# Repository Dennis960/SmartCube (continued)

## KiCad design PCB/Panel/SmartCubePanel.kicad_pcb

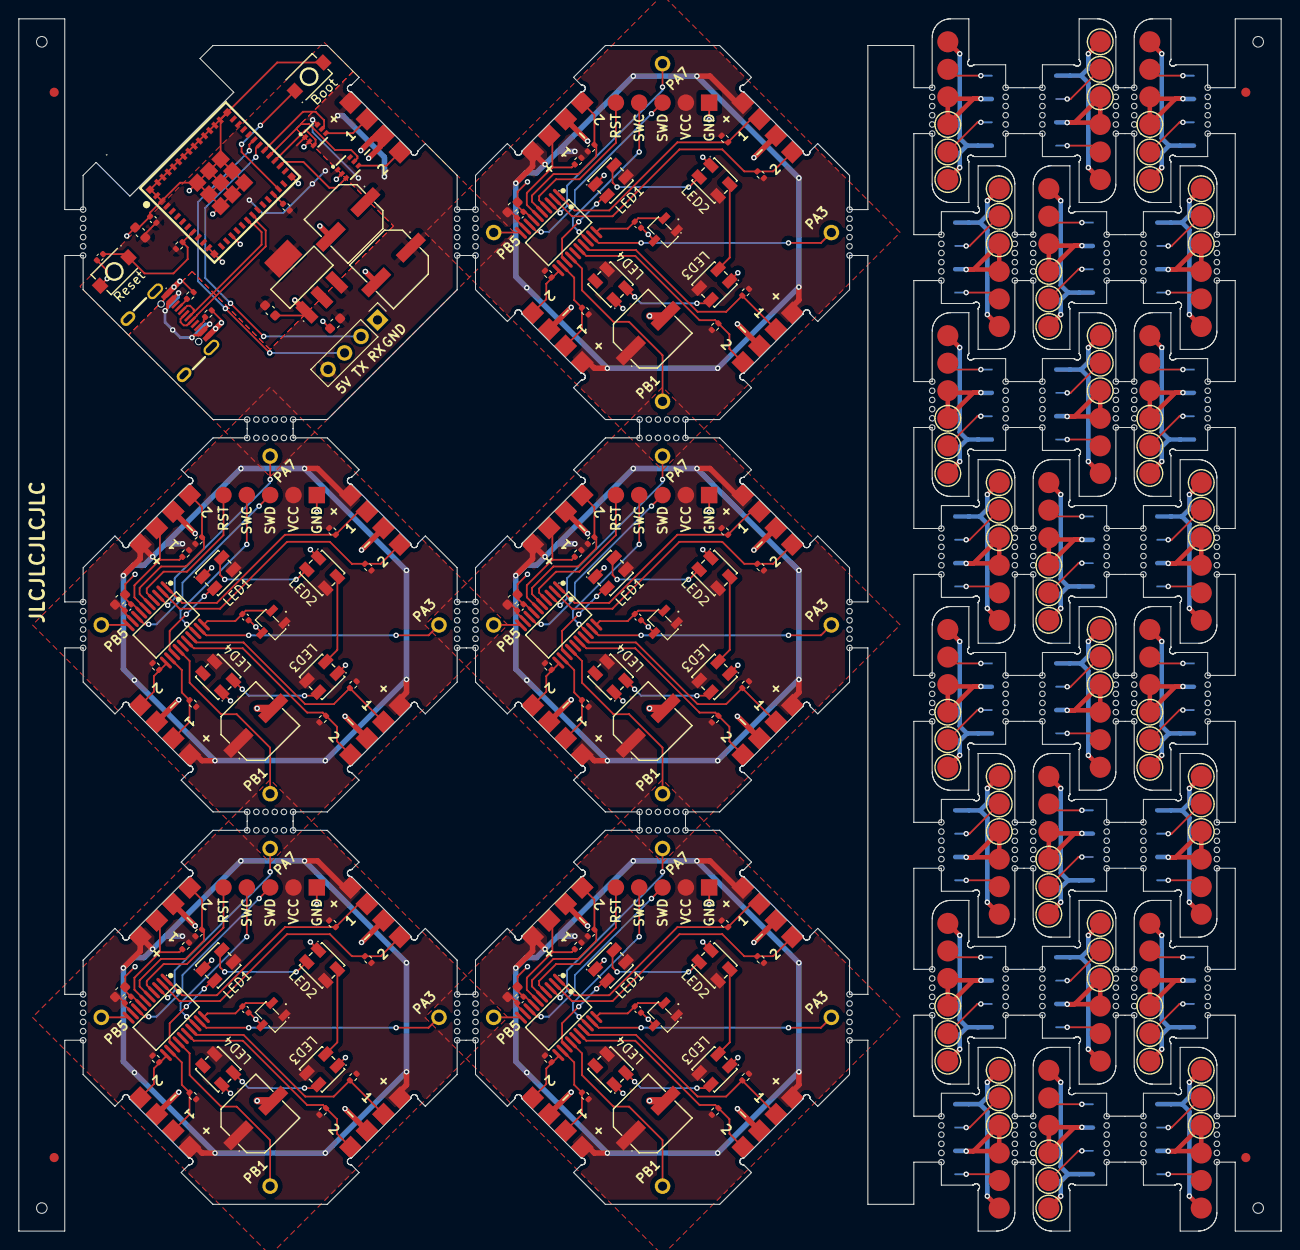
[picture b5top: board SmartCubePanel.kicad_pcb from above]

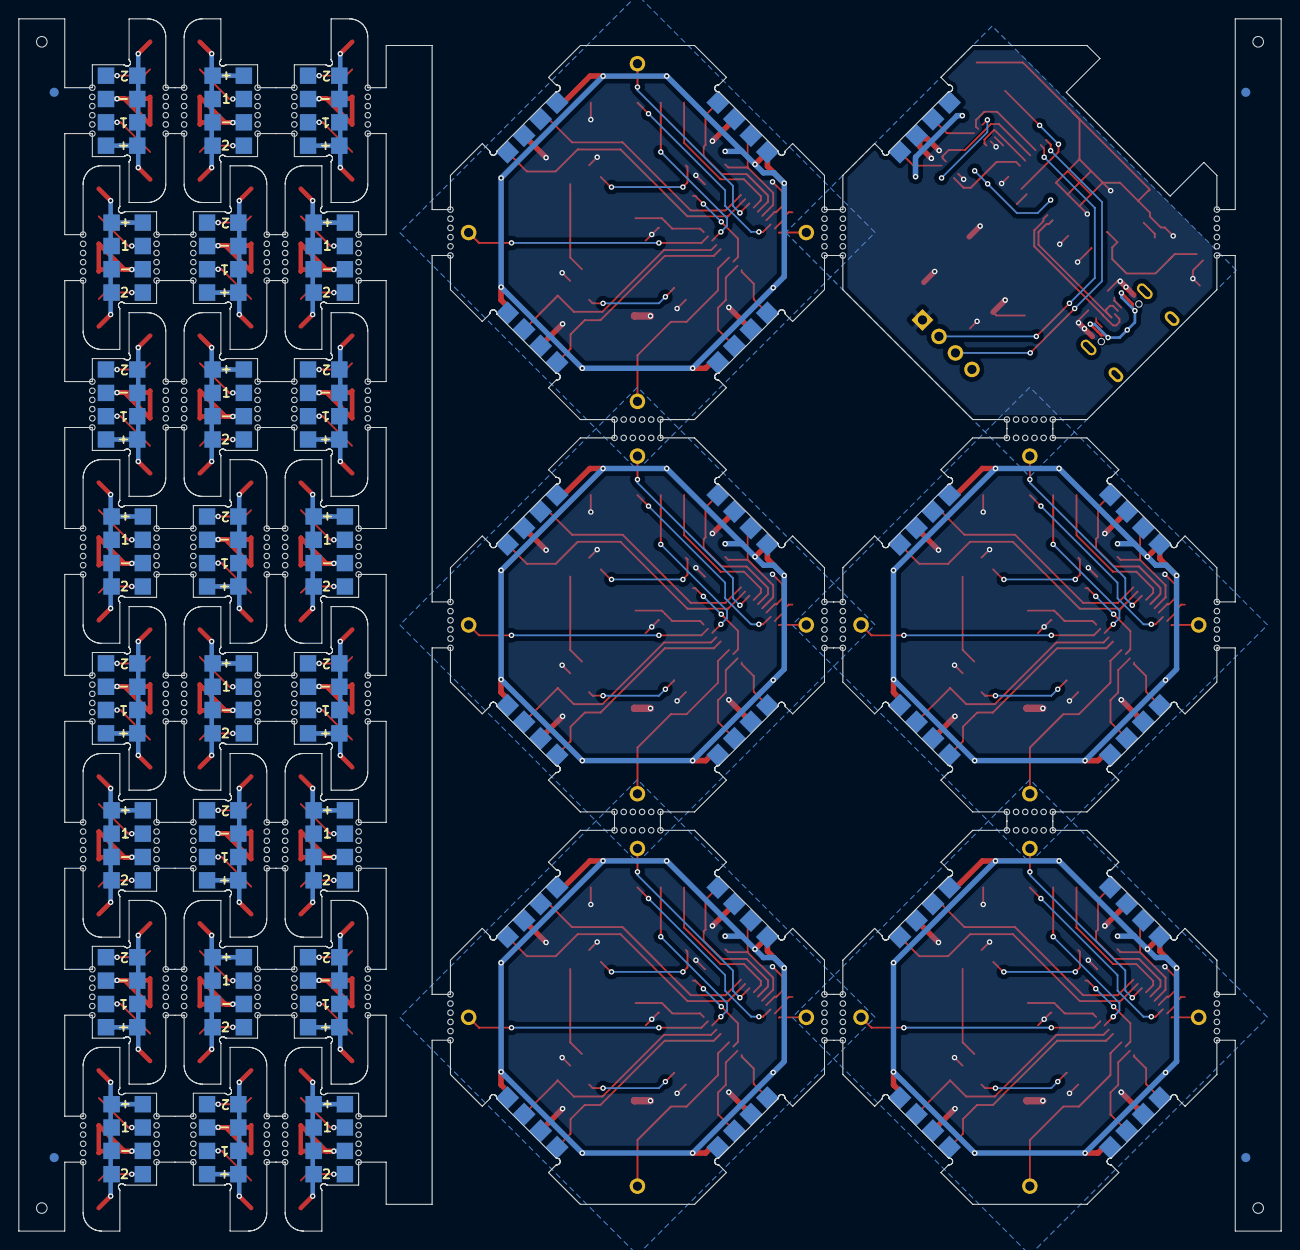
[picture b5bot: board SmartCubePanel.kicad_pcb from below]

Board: 2 copper layers, 137.5 x 132.0 mm, 767 parts (52 on the bottom side), 224 nets.

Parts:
KiKit_FID_B_1, KiKit_FID_B_2, KiKit_FID_B_3, KiKit_FID_B_4: Fiducial
KiKit_FID_T_1, KiKit_FID_T_2, KiKit_FID_T_3, KiKit_FID_T_4: Fiducial
KiKit_MB_1_1, KiKit_MB_1_2, KiKit_MB_1_3, KiKit_MB_1_4, KiKit_MB_1_5, KiKit_MB_1_6, KiKit_MB_2_1, KiKit_MB_2_2, KiKit_MB_2_3, KiKit_MB_2_4, KiKit_MB_2_5, KiKit_MB_2_6, KiKit_MB_3_1, KiKit_MB_3_2, KiKit_MB_3_3, KiKit_MB_3_4, KiKit_MB_3_5, KiKit_MB_3_6, KiKit_MB_4_1, KiKit_MB_4_2, KiKit_MB_4_3, KiKit_MB_4_4, KiKit_MB_4_5, KiKit_MB_4_6, KiKit_MB_5_1, KiKit_MB_5_2, KiKit_MB_5_3, KiKit_MB_5_4, KiKit_MB_5_5, KiKit_MB_5_6, KiKit_MB_6_1, KiKit_MB_6_2, KiKit_MB_6_3, KiKit_MB_6_4, KiKit_MB_6_5, KiKit_MB_6_6, KiKit_MB_7_1, KiKit_MB_7_2, KiKit_MB_7_3, KiKit_MB_7_4, KiKit_MB_7_5, KiKit_MB_7_6, KiKit_MB_8_1, KiKit_MB_8_2, KiKit_MB_8_3, KiKit_MB_8_4, KiKit_MB_8_5, KiKit_MB_8_6, KiKit_MB_9_1, KiKit_MB_9_2, KiKit_MB_9_3, KiKit_MB_9_4, KiKit_MB_9_5, KiKit_MB_9_6, KiKit_MB_10_1, KiKit_MB_10_2, KiKit_MB_10_3, KiKit_MB_10_4, KiKit_MB_10_5, KiKit_MB_10_6, KiKit_MB_11_1, KiKit_MB_11_2, KiKit_MB_11_3, KiKit_MB_11_4, KiKit_MB_11_5, KiKit_MB_11_6, KiKit_MB_12_1, KiKit_MB_12_2, KiKit_MB_12_3, KiKit_MB_12_4, KiKit_MB_12_5, KiKit_MB_12_6, KiKit_MB_13_1, KiKit_MB_13_2, KiKit_MB_13_3, KiKit_MB_13_4, KiKit_MB_13_5, KiKit_MB_13_6, KiKit_MB_14_1, KiKit_MB_14_2, KiKit_MB_14_3, KiKit_MB_14_4, KiKit_MB_14_5, KiKit_MB_14_6, KiKit_MB_15_1, KiKit_MB_15_2, KiKit_MB_15_3, KiKit_MB_15_4, KiKit_MB_15_5, KiKit_MB_15_6, KiKit_MB_16_1, KiKit_MB_16_2, KiKit_MB_16_3, KiKit_MB_16_4, KiKit_MB_16_5, KiKit_MB_16_6, KiKit_MB_17_1, KiKit_MB_17_2, KiKit_MB_17_3, KiKit_MB_17_4, KiKit_MB_17_5, KiKit_MB_17_6, KiKit_MB_18_1, KiKit_MB_18_2, KiKit_MB_18_3, KiKit_MB_18_4, KiKit_MB_18_5, KiKit_MB_18_6, KiKit_MB_19_1, KiKit_MB_19_2, KiKit_MB_19_3, KiKit_MB_19_4, KiKit_MB_19_5, KiKit_MB_19_6, KiKit_MB_20_1, KiKit_MB_20_2, KiKit_MB_20_3, KiKit_MB_20_4, KiKit_MB_20_5, KiKit_MB_20_6, KiKit_MB_21_1, KiKit_MB_21_2, KiKit_MB_21_3, KiKit_MB_21_4, KiKit_MB_21_5, KiKit_MB_21_6, KiKit_MB_22_1, KiKit_MB_22_2, KiKit_MB_22_3, KiKit_MB_22_4, KiKit_MB_22_5, KiKit_MB_22_6, KiKit_MB_23_1, KiKit_MB_23_2, KiKit_MB_23_3, KiKit_MB_23_4, KiKit_MB_23_5, KiKit_MB_23_6, KiKit_MB_24_1, KiKit_MB_24_2, KiKit_MB_24_3, KiKit_MB_24_4, KiKit_MB_24_5, KiKit_MB_24_6, KiKit_MB_25_1, KiKit_MB_25_2, KiKit_MB_25_3, KiKit_MB_25_4, KiKit_MB_25_5, KiKit_MB_25_6, KiKit_MB_26_1, KiKit_MB_26_2, KiKit_MB_26_3, KiKit_MB_26_4, KiKit_MB_26_5, KiKit_MB_26_6, KiKit_MB_27_1, KiKit_MB_27_2, KiKit_MB_27_3, KiKit_MB_27_4, KiKit_MB_27_5, KiKit_MB_27_6, KiKit_MB_28_1, KiKit_MB_28_2, KiKit_MB_28_3, KiKit_MB_28_4, KiKit_MB_28_5, KiKit_MB_28_6, KiKit_MB_29_1, KiKit_MB_29_2, KiKit_MB_29_3, KiKit_MB_29_4, KiKit_MB_29_5, KiKit_MB_29_6, KiKit_MB_30_1, KiKit_MB_30_2, KiKit_MB_30_3, KiKit_MB_30_4, KiKit_MB_30_5, KiKit_MB_30_6, KiKit_MB_31_1, KiKit_MB_31_2, KiKit_MB_31_3, KiKit_MB_31_4, KiKit_MB_31_5, KiKit_MB_31_6, KiKit_MB_32_1, KiKit_MB_32_2, KiKit_MB_32_3, KiKit_MB_32_4, KiKit_MB_32_5, KiKit_MB_32_6, KiKit_MB_33_1, KiKit_MB_33_2, KiKit_MB_33_3, KiKit_MB_33_4, KiKit_MB_33_5, KiKit_MB_33_6, KiKit_MB_34_1, KiKit_MB_34_2, KiKit_MB_34_3, KiKit_MB_34_4, KiKit_MB_34_5, KiKit_MB_34_6, KiKit_MB_35_1, KiKit_MB_35_2, KiKit_MB_35_3, KiKit_MB_35_4, KiKit_MB_35_5, KiKit_MB_35_6, KiKit_MB_36_1, KiKit_MB_36_2, KiKit_MB_36_3, KiKit_MB_36_4, KiKit_MB_36_5, KiKit_MB_36_6, KiKit_MB_37_1, KiKit_MB_37_2, KiKit_MB_37_3, KiKit_MB_37_4, KiKit_MB_37_5, KiKit_MB_37_6, KiKit_MB_38_1, KiKit_MB_38_2, KiKit_MB_38_3, KiKit_MB_38_4, KiKit_MB_38_5, KiKit_MB_38_6, KiKit_MB_39_1, KiKit_MB_39_2, KiKit_MB_39_3, KiKit_MB_39_4, KiKit_MB_39_5, KiKit_MB_39_6, KiKit_MB_40_1, KiKit_MB_40_2, KiKit_MB_40_3, KiKit_MB_40_4, KiKit_MB_40_5, KiKit_MB_40_6, KiKit_MB_41_1, KiKit_MB_41_2, KiKit_MB_41_3, KiKit_MB_41_4, KiKit_MB_41_5, KiKit_MB_41_6, KiKit_MB_42_1, KiKit_MB_42_2, KiKit_MB_42_3, KiKit_MB_42_4, KiKit_MB_42_5, KiKit_MB_42_6, KiKit_MB_43_1, KiKit_MB_43_2, KiKit_MB_43_3, KiKit_MB_43_4, KiKit_MB_43_5, KiKit_MB_43_6, KiKit_MB_44_1, KiKit_MB_44_2, KiKit_MB_44_3, KiKit_MB_44_4, KiKit_MB_44_5, KiKit_MB_44_6, KiKit_MB_45_1, KiKit_MB_45_2, KiKit_MB_45_3, KiKit_MB_45_4, KiKit_MB_45_5, KiKit_MB_45_6, KiKit_MB_46_1, KiKit_MB_46_2, KiKit_MB_46_3, KiKit_MB_46_4, KiKit_MB_46_5, KiKit_MB_46_6, KiKit_MB_47_1, KiKit_MB_47_2, KiKit_MB_47_3, KiKit_MB_47_4, KiKit_MB_47_5, KiKit_MB_47_6, KiKit_MB_48_1, KiKit_MB_48_2, KiKit_MB_48_3, KiKit_MB_48_4, KiKit_MB_48_5, KiKit_MB_48_6, KiKit_MB_49_1, KiKit_MB_49_2, KiKit_MB_49_3, KiKit_MB_49_4, KiKit_MB_49_5, KiKit_MB_49_6, KiKit_MB_50_1, KiKit_MB_50_2, KiKit_MB_50_3, KiKit_MB_50_4, KiKit_MB_50_5, KiKit_MB_50_6, KiKit_MB_51_1, KiKit_MB_51_2, KiKit_MB_51_3, KiKit_MB_51_4, KiKit_MB_51_5, KiKit_MB_51_6, KiKit_MB_52_1, KiKit_MB_52_2, KiKit_MB_52_3, KiKit_MB_52_4, KiKit_MB_52_5, KiKit_MB_52_6, KiKit_MB_53_1, KiKit_MB_53_2, KiKit_MB_53_3, KiKit_MB_53_4, KiKit_MB_53_5, KiKit_MB_53_6, KiKit_MB_54_1, KiKit_MB_54_2, KiKit_MB_54_3, KiKit_MB_54_4, KiKit_MB_54_5, KiKit_MB_54_6, KiKit_MB_55_1, KiKit_MB_55_2, KiKit_MB_55_3, KiKit_MB_55_4, KiKit_MB_55_5, KiKit_MB_55_6, KiKit_MB_56_1, KiKit_MB_56_2, KiKit_MB_56_3, KiKit_MB_56_4, KiKit_MB_56_5, KiKit_MB_56_6, KiKit_MB_57_1, KiKit_MB_57_2, KiKit_MB_57_3, KiKit_MB_57_4, KiKit_MB_57_5, KiKit_MB_57_6, KiKit_MB_58_1, KiKit_MB_58_2, KiKit_MB_58_3, KiKit_MB_58_4, KiKit_MB_58_5, KiKit_MB_58_6, KiKit_MB_59_1, KiKit_MB_59_2, KiKit_MB_59_3, KiKit_MB_59_4, KiKit_MB_59_5, KiKit_MB_59_6, KiKit_MB_60_1, KiKit_MB_60_2, KiKit_MB_60_3, KiKit_MB_60_4, KiKit_MB_60_5, KiKit_MB_60_6, KiKit_MB_61_1, KiKit_MB_61_2, KiKit_MB_61_3, KiKit_MB_61_4, KiKit_MB_61_5, KiKit_MB_61_6, KiKit_MB_62_1, KiKit_MB_62_2, KiKit_MB_62_3, KiKit_MB_62_4, KiKit_MB_62_5, KiKit_MB_62_6, KiKit_MB_63_1, KiKit_MB_63_2, KiKit_MB_63_3, KiKit_MB_63_4, KiKit_MB_63_5, KiKit_MB_63_6, KiKit_MB_64_1, KiKit_MB_64_2, KiKit_MB_64_3, KiKit_MB_64_4, KiKit_MB_64_5, KiKit_MB_64_6, KiKit_MB_65_1, KiKit_MB_65_2, KiKit_MB_65_3, KiKit_MB_65_4, KiKit_MB_65_5, KiKit_MB_65_6, KiKit_MB_66_1, KiKit_MB_66_2, KiKit_MB_66_3, KiKit_MB_66_4, KiKit_MB_66_5, KiKit_MB_66_6, KiKit_MB_67_1, KiKit_MB_67_2, KiKit_MB_67_3, KiKit_MB_67_4, KiKit_MB_67_5, KiKit_MB_67_6, KiKit_MB_68_1, KiKit_MB_68_2, KiKit_MB_68_3, KiKit_MB_68_4, KiKit_MB_68_5, KiKit_MB_68_6: NPTH
KiKit_TO_1, KiKit_TO_2, KiKit_TO_3, KiKit_TO_4: NPTH
M_1_C1, M_2_C1, M_3_C1, M_4_C1, M_5_C1: 10uF; C_0603_1608Metric
M_1_C2, M_2_C2, M_3_C2, M_4_C2, M_5_C2: 100nF; C_0402_1005Metric
M_1_C3, M_2_C3, M_3_C3, M_4_C3, M_5_C3: 10nF; C_0402_1005Metric
M_1_C4, M_2_C4, M_3_C4, M_4_C4, M_5_C4: 470uF Electrolytic; CAP-SMD_BD6.3-L6.6-W6.6-FD
M_1_J1, M_2_J1, M_3_J1, M_4_J1, M_5_J1: SWD_Programmer; SWD_Pad
M_1_J2, M_1_J3, M_1_J4, M_1_J5, M_2_J2, M_2_J3, M_2_J4, M_2_J5, M_3_J2, M_3_J3, M_3_J4, M_3_J5, M_4_J2, M_4_J3, M_4_J4, M_4_J5, M_5_J2, M_5_J3, M_5_J4, M_5_J5: Conn_01x01; ShieldConnector
M_1_LED1, M_1_LED2, M_1_LED3, M_1_LED4, M_2_LED1, M_2_LED2, M_2_LED3, M_2_LED4, M_3_LED1, M_3_LED2, M_3_LED3, M_3_LED4, M_4_LED1, M_4_LED2, M_4_LED3, M_4_LED4, M_5_LED1, M_5_LED2, M_5_LED3, M_5_LED4: SK6812MINI-HS; LED-SK6812MINI-HS
M_1_PinHeaderBottom1, M_1_PinHeaderLeft1, M_1_PinHeaderRight1, M_1_PinHeaderTop1, M_2_PinHeaderBottom1, M_2_PinHeaderLeft1, M_2_PinHeaderRight1, M_2_PinHeaderTop1, M_3_PinHeaderBottom1, M_3_PinHeaderLeft1, M_3_PinHeaderRight1, M_3_PinHeaderTop1, M_4_PinHeaderBottom1, M_4_PinHeaderLeft1, M_4_PinHeaderRight1, M_4_PinHeaderTop1, M_5_PinHeaderBottom1, M_5_PinHeaderLeft1, M_5_PinHeaderRight1, M_5_PinHeaderTop1: PinHeader; 01x04_PinPads
M_1_R1, M_1_R2, M_1_R3, M_1_R4, M_1_R5, M_1_R6, M_1_R7, M_1_R8, M_2_R1, M_2_R2, M_2_R3, M_2_R4, M_2_R5, M_2_R6, M_2_R7, M_2_R8, M_3_R1, M_3_R2, M_3_R3, M_3_R4, M_3_R5, M_3_R6, M_3_R7, M_3_R8, M_4_R1, M_4_R2, M_4_R3, M_4_R4, M_4_R5, M_4_R6, M_4_R7, M_4_R8, M_5_R1, M_5_R2, M_5_R3, M_5_R4, M_5_R5, M_5_R6, M_5_R7, M_5_R8: 10k; R_0402_1005Metric
M_1_U1, M_2_U1, M_3_U1, M_4_U1, M_5_U1: PY32F002BF15P6TU; Py32
M_1_U6, M_2_U6, M_3_U6, M_4_U6, M_5_U6: HallLinearSensor
POGO_6_J1, POGO_6_J3, POGO_6_J4, POGO_7_J1, POGO_7_J3, POGO_7_J4, POGO_8_J1, POGO_8_J3, POGO_8_J4, POGO_9_J1, POGO_9_J3, POGO_9_J4, POGO_10_J1, POGO_10_J3, POGO_10_J4, POGO_11_J1, POGO_11_J3, POGO_11_J4, POGO_12_J1, POGO_12_J3, POGO_12_J4, POGO_13_J1, POGO_13_J3, POGO_13_J4, POGO_14_J1, POGO_14_J3, POGO_14_J4, POGO_15_J1, POGO_15_J3, POGO_15_J4, POGO_16_J1, POGO_16_J3, POGO_16_J4, POGO_17_J1, POGO_17_J3, POGO_17_J4, POGO_18_J1, POGO_18_J3, POGO_18_J4, POGO_19_J1, POGO_19_J3, POGO_19_J4, POGO_20_J1, POGO_20_J3, POGO_20_J4, POGO_21_J1, POGO_21_J3, POGO_21_J4, POGO_22_J1, POGO_22_J3, POGO_22_J4, POGO_23_J1, POGO_23_J3, POGO_23_J4, POGO_24_J1, POGO_24_J3, POGO_24_J4, POGO_25_J1, POGO_25_J3, POGO_25_J4, POGO_26_J1, POGO_26_J3, POGO_26_J4, POGO_27_J1, POGO_27_J3, POGO_27_J4, POGO_28_J1, POGO_28_J3, POGO_28_J4, POGO_29_J1, POGO_29_J3, POGO_29_J4: PogoPinPad
POGO_6_J2, POGO_6_J5, POGO_7_J2, POGO_7_J5, POGO_8_J2, POGO_8_J5, POGO_9_J2, POGO_9_J5, POGO_10_J2, POGO_10_J5, POGO_11_J2, POGO_11_J5, POGO_12_J2, POGO_12_J5, POGO_13_J2, POGO_13_J5, POGO_14_J2, POGO_14_J5, POGO_15_J2, POGO_15_J5, POGO_16_J2, POGO_16_J5, POGO_17_J2, POGO_17_J5, POGO_18_J2, POGO_18_J5, POGO_19_J2, POGO_19_J5, POGO_20_J2, POGO_20_J5, POGO_21_J2, POGO_21_J5, POGO_22_J2, POGO_22_J5, POGO_23_J2, POGO_23_J5, POGO_24_J2, POGO_24_J5, POGO_25_J2, POGO_25_J5, POGO_26_J2, POGO_26_J5, POGO_27_J2, POGO_27_J5, POGO_28_J2, POGO_28_J5, POGO_29_J2, POGO_29_J5: Conn_01x06; 01x04_PinPads_Single
POGO_6_U1, POGO_6_U2, POGO_6_U3, POGO_7_U1, POGO_7_U2, POGO_7_U3, POGO_8_U1, POGO_8_U2, POGO_8_U3, POGO_9_U1, POGO_9_U2, POGO_9_U3, POGO_10_U1, POGO_10_U2, POGO_10_U3, POGO_11_U1, POGO_11_U2, POGO_11_U3, POGO_12_U1, POGO_12_U2, POGO_12_U3, POGO_13_U1, POGO_13_U2, POGO_13_U3, POGO_14_U1, POGO_14_U2, POGO_14_U3, POGO_15_U1, POGO_15_U2, POGO_15_U3, POGO_16_U1, POGO_16_U2, POGO_16_U3, POGO_17_U1, POGO_17_U2, POGO_17_U3, POGO_18_U1, POGO_18_U2, POGO_18_U3, POGO_19_U1, POGO_19_U2, POGO_19_U3, POGO_20_U1, POGO_20_U2, POGO_20_U3, POGO_21_U1, POGO_21_U2, POGO_21_U3, POGO_22_U1, POGO_22_U2, POGO_22_U3, POGO_23_U1, POGO_23_U2, POGO_23_U3, POGO_24_U1, POGO_24_U2, POGO_24_U3, POGO_25_U1, POGO_25_U2, POGO_25_U3, POGO_26_U1, POGO_26_U2, POGO_26_U3, POGO_27_U1, POGO_27_U2, POGO_27_U3, POGO_28_U1, POGO_28_U2, POGO_28_U3, POGO_29_U1, POGO_29_U2, POGO_29_U3: PogoPin
PSU_0_C1: 100nF-Ceramic; C_0402_1005Metric
PSU_0_C2, PSU_0_C4, PSU_0_C5: 10uF; C_0603_1608Metric
PSU_0_C3: 10nF; C_0402_1005Metric
PSU_0_C6, PSU_0_C7: ElectrolyticCapacitorSMD; CAP-SMD_BD6.3-L6.6-W6.6-FD
PSU_0_J1: Conn_01x03; PinHeader_1x04_P2.54mm_Vertical
PSU_0_R1, PSU_0_R2: 10k; R_0402_1005Metric
PSU_0_R3, PSU_0_R4: 5k1; R_0402_1005Metric
PSU_0_U2, PSU_0_U3: Tactile-Switch; Button
PSU_0_U4: ESP32-C6-MINI-1-N4; ESP32C6-Mini-1-N4
PSU_0_U5, PSU_0_U8: BidirectionalLogicLevelShifter; BidirectionalLogicLevelConverter
PSU_0_U6: LinearVoltageRegulator; VoltageRegulator
PSU_0_U7: USB-TypeC; USB-C-SMD_TYPE-C-6PIN-2MD-073
PSU_0_U9: PinHeaderRight; 01x04_PinPads

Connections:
Board_0-+3.3V: PSU_0_C2.1, PSU_0_C3.1, PSU_0_C5.1, PSU_0_R1.1, PSU_0_R2.2, PSU_0_U4.3 (3V3), PSU_0_U5.1 (VCCA), PSU_0_U6.2 (VOUT), PSU_0_U6.4 (VOUT), PSU_0_U8.1 (VCCA)
Board_0-+5V: PSU_0_C4.2, PSU_0_C6.1, PSU_0_C7.1, PSU_0_J1.4, PSU_0_U5.6 (VCCB), PSU_0_U6.3 (VIN), PSU_0_U7.2 (VBUS), PSU_0_U7.11 (VBUS), PSU_0_U8.6 (VCCB), PSU_0_U9.1
Board_0-/DataTop1_3V3: PSU_0_U4.26 (IO20), PSU_0_U5.3 (A)
Board_0-/DataTop1_5V: PSU_0_U5.4 (B), PSU_0_U9.4
Board_0-/DataTop2_3V3: PSU_0_U4.27 (IO21), PSU_0_U8.3 (A)
Board_0-/DataTop2_5V: PSU_0_U8.4 (B), PSU_0_U9.2
Board_0-DIR1: PSU_0_U4.28 (IO22), PSU_0_U5.5 (DIR)
Board_0-DIR2: PSU_0_U4.29 (IO23), PSU_0_U8.5 (DIR)
Board_0-EN: PSU_0_C1.1, PSU_0_R1.2, PSU_0_U2.2, PSU_0_U4.8 (EN)
Board_0-GND: PSU_0_C1.2, PSU_0_C2.2, PSU_0_C3.2, PSU_0_C4.1, PSU_0_C5.2, PSU_0_C6.2, PSU_0_C7.2, PSU_0_J1.1, PSU_0_R3.1, PSU_0_R4.1, PSU_0_U2.1, PSU_0_U3.1, PSU_0_U4.1 (GND), PSU_0_U4.2 (GND), PSU_0_U4.11 (GND), PSU_0_U4.14 (GND), PSU_0_U4.36 (GND), PSU_0_U4.37 (GND), PSU_0_U4.38 (GND), PSU_0_U4.39 (GND), PSU_0_U4.40 (GND), PSU_0_U4.41 (GND), PSU_0_U4.42 (GND), PSU_0_U4.43 (GND), PSU_0_U4.44 (GND), PSU_0_U4.45 (GND), PSU_0_U4.46 (GND), PSU_0_U4.47 (GND), PSU_0_U4.48 (GND), PSU_0_U4.49 (GND), PSU_0_U4.50 (GND), PSU_0_U4.51 (GND), PSU_0_U4.52 (GND), PSU_0_U4.53 (GND), PSU_0_U5.2 (GND), PSU_0_U6.1 (GND), PSU_0_U7.1 (GND), PSU_0_U7.12 (GND), PSU_0_U8.2 (GND), PSU_0_U9.3
Board_0-IO8: PSU_0_R2.1, PSU_0_U4.22 (IO8)
Board_0-IO9: PSU_0_U3.2, PSU_0_U4.23 (IO9)
Board_0-PWR_USB_CC1: PSU_0_R3.2, PSU_0_U7.4 (CC1)
Board_0-PWR_USB_CC2: PSU_0_R4.2, PSU_0_U7.10 (CC2)
Board_0-RX: PSU_0_J1.2, PSU_0_U4.30 (RXD0)
Board_0-TX: PSU_0_J1.3, PSU_0_U4.31 (TXD0)
Board_0-USB_D+: PSU_0_U4.18 (IO13), PSU_0_U7.6 (DP1), PSU_0_U7.8 (DP2)
Board_0-USB_D-: PSU_0_U4.17 (IO12), PSU_0_U7.5 (DN2), PSU_0_U7.7 (DN1)
Board_1-+5V: M_1_C1.2, M_1_C2.2, M_1_C4.1, M_1_J1.2, M_1_LED1.3 (VDD), M_1_LED2.3 (VDD), M_1_LED3.3 (VDD), M_1_LED4.3 (VDD), M_1_PinHeaderBottom1.1, M_1_PinHeaderLeft1.1, M_1_PinHeaderRight1.1, M_1_PinHeaderTop1.1, M_1_R1.1, M_1_R2.1, M_1_R3.1, M_1_R4.1, M_1_R5.1, M_1_R6.1, M_1_R7.1, M_1_R8.1, M_1_U1.9 (VCC), M_1_U6.1 (VDD)
Board_1-/DataBottom1: M_1_PinHeaderBottom1.2, M_1_R6.2, M_1_U1.17 (PA1)
Board_1-/DataBottom2: M_1_PinHeaderBottom1.4, M_1_R5.2, M_1_U1.16 (PA0)
Board_1-/DataLeft1: M_1_PinHeaderLeft1.2, M_1_R8.2, M_1_U1.12 (PB3)
Board_1-/DataLeft2: M_1_PinHeaderLeft1.4, M_1_R7.2, M_1_U1.11 (PB4)
Board_1-/DataRight1: M_1_PinHeaderRight1.2, M_1_R4.2, M_1_U1.1 (PA5)
Board_1-/DataRight2: M_1_PinHeaderRight1.4, M_1_R3.2, M_1_U1.2 (PA6)
Board_1-/DataTop1: M_1_PinHeaderTop1.2, M_1_R2.2, M_1_U1.6 (PB7)
Board_1-/DataTop2: M_1_PinHeaderTop1.4, M_1_R1.2, M_1_U1.5 (PC1)
Board_1-/HallAdc: M_1_C3.2, M_1_U1.20 (PA4), M_1_U6.3 (OUT)
Board_1-/LedIn: M_1_LED1.2 (DIN), M_1_U1.13 (PB2)
Board_1-/Reset: M_1_J1.5, M_1_U1.4 (PC0-NRST)
Board_1-/SWC: M_1_J1.4, M_1_U1.18 (PA2-SWC)
Board_1-/SWD: M_1_J1.3, M_1_U1.8 (PB6-SWD)
Board_1-/ShieldBottomLeft: M_1_J3.1, M_1_U1.14 (PB1)
Board_1-/ShieldBottomRight: M_1_J5.1, M_1_U1.19 (PA3)
Board_1-/ShieldTopLeft: M_1_J2.1, M_1_U1.10 (PB5)
Board_1-/ShieldTopRight: M_1_J4.1, M_1_U1.3 (PA7)
Board_1-GND: M_1_C1.1, M_1_C2.1, M_1_C3.1, M_1_C4.2, M_1_J1.1, M_1_LED1.1 (GND), M_1_LED2.1 (GND), M_1_LED3.1 (GND), M_1_LED4.1 (GND), M_1_PinHeaderBottom1.3, M_1_PinHeaderLeft1.3, M_1_PinHeaderRight1.3, M_1_PinHeaderTop1.3, M_1_U1.7 (VSS), M_1_U6.2 (GND)
Board_1-Net-(LED1-DOUT): M_1_LED1.4 (DOUT), M_1_LED2.2 (DIN)
Board_1-Net-(LED2-DOUT): M_1_LED2.4 (DOUT), M_1_LED3.2 (DIN)
Board_1-Net-(LED3-DOUT): M_1_LED3.4 (DOUT), M_1_LED4.2 (DIN)
Board_2-+5V: M_2_C1.2, M_2_C2.2, M_2_C4.1, M_2_J1.2, M_2_LED1.3 (VDD), M_2_LED2.3 (VDD), M_2_LED3.3 (VDD), M_2_LED4.3 (VDD), M_2_PinHeaderBottom1.1, M_2_PinHeaderLeft1.1, M_2_PinHeaderRight1.1, M_2_PinHeaderTop1.1, M_2_R1.1, M_2_R2.1, M_2_R3.1, M_2_R4.1, M_2_R5.1, M_2_R6.1, M_2_R7.1, M_2_R8.1, M_2_U1.9 (VCC), M_2_U6.1 (VDD)
Board_2-/DataBottom1: M_2_PinHeaderBottom1.2, M_2_R6.2, M_2_U1.17 (PA1)
Board_2-/DataBottom2: M_2_PinHeaderBottom1.4, M_2_R5.2, M_2_U1.16 (PA0)
Board_2-/DataLeft1: M_2_PinHeaderLeft1.2, M_2_R8.2, M_2_U1.12 (PB3)
Board_2-/DataLeft2: M_2_PinHeaderLeft1.4, M_2_R7.2, M_2_U1.11 (PB4)
Board_2-/DataRight1: M_2_PinHeaderRight1.2, M_2_R4.2, M_2_U1.1 (PA5)
Board_2-/DataRight2: M_2_PinHeaderRight1.4, M_2_R3.2, M_2_U1.2 (PA6)
Board_2-/DataTop1: M_2_PinHeaderTop1.2, M_2_R2.2, M_2_U1.6 (PB7)
Board_2-/DataTop2: M_2_PinHeaderTop1.4, M_2_R1.2, M_2_U1.5 (PC1)
Board_2-/HallAdc: M_2_C3.2, M_2_U1.20 (PA4), M_2_U6.3 (OUT)
Board_2-/LedIn: M_2_LED1.2 (DIN), M_2_U1.13 (PB2)
Board_2-/Reset: M_2_J1.5, M_2_U1.4 (PC0-NRST)
Board_2-/SWC: M_2_J1.4, M_2_U1.18 (PA2-SWC)
Board_2-/SWD: M_2_J1.3, M_2_U1.8 (PB6-SWD)
Board_2-/ShieldBottomLeft: M_2_J3.1, M_2_U1.14 (PB1)
Board_2-/ShieldBottomRight: M_2_J5.1, M_2_U1.19 (PA3)
Board_2-/ShieldTopLeft: M_2_J2.1, M_2_U1.10 (PB5)
Board_2-/ShieldTopRight: M_2_J4.1, M_2_U1.3 (PA7)
Board_2-GND: M_2_C1.1, M_2_C2.1, M_2_C3.1, M_2_C4.2, M_2_J1.1, M_2_LED1.1 (GND), M_2_LED2.1 (GND), M_2_LED3.1 (GND), M_2_LED4.1 (GND), M_2_PinHeaderBottom1.3, M_2_PinHeaderLeft1.3, M_2_PinHeaderRight1.3, M_2_PinHeaderTop1.3, M_2_U1.7 (VSS), M_2_U6.2 (GND)
Board_2-Net-(LED1-DOUT): M_2_LED1.4 (DOUT), M_2_LED2.2 (DIN)
Board_2-Net-(LED2-DOUT): M_2_LED2.4 (DOUT), M_2_LED3.2 (DIN)
Board_2-Net-(LED3-DOUT): M_2_LED3.4 (DOUT), M_2_LED4.2 (DIN)
Board_3-+5V: M_3_C1.2, M_3_C2.2, M_3_C4.1, M_3_J1.2, M_3_LED1.3 (VDD), M_3_LED2.3 (VDD), M_3_LED3.3 (VDD), M_3_LED4.3 (VDD), M_3_PinHeaderBottom1.1, M_3_PinHeaderLeft1.1, M_3_PinHeaderRight1.1, M_3_PinHeaderTop1.1, M_3_R1.1, M_3_R2.1, M_3_R3.1, M_3_R4.1, M_3_R5.1, M_3_R6.1, M_3_R7.1, M_3_R8.1, M_3_U1.9 (VCC), M_3_U6.1 (VDD)
Board_3-/DataBottom1: M_3_PinHeaderBottom1.2, M_3_R6.2, M_3_U1.17 (PA1)
Board_3-/DataBottom2: M_3_PinHeaderBottom1.4, M_3_R5.2, M_3_U1.16 (PA0)
Board_3-/DataLeft1: M_3_PinHeaderLeft1.2, M_3_R8.2, M_3_U1.12 (PB3)
Board_3-/DataLeft2: M_3_PinHeaderLeft1.4, M_3_R7.2, M_3_U1.11 (PB4)
Board_3-/DataRight1: M_3_PinHeaderRight1.2, M_3_R4.2, M_3_U1.1 (PA5)
Board_3-/DataRight2: M_3_PinHeaderRight1.4, M_3_R3.2, M_3_U1.2 (PA6)
Board_3-/DataTop1: M_3_PinHeaderTop1.2, M_3_R2.2, M_3_U1.6 (PB7)
Board_3-/DataTop2: M_3_PinHeaderTop1.4, M_3_R1.2, M_3_U1.5 (PC1)
Board_3-/HallAdc: M_3_C3.2, M_3_U1.20 (PA4), M_3_U6.3 (OUT)
Board_3-/LedIn: M_3_LED1.2 (DIN), M_3_U1.13 (PB2)
Board_3-/Reset: M_3_J1.5, M_3_U1.4 (PC0-NRST)
Board_3-/SWC: M_3_J1.4, M_3_U1.18 (PA2-SWC)
Board_3-/SWD: M_3_J1.3, M_3_U1.8 (PB6-SWD)
Board_3-/ShieldBottomLeft: M_3_J3.1, M_3_U1.14 (PB1)
Board_3-/ShieldBottomRight: M_3_J5.1, M_3_U1.19 (PA3)
Board_3-/ShieldTopLeft: M_3_J2.1, M_3_U1.10 (PB5)
Board_3-/ShieldTopRight: M_3_J4.1, M_3_U1.3 (PA7)
Board_3-GND: M_3_C1.1, M_3_C2.1, M_3_C3.1, M_3_C4.2, M_3_J1.1, M_3_LED1.1 (GND), M_3_LED2.1 (GND), M_3_LED3.1 (GND), M_3_LED4.1 (GND), M_3_PinHeaderBottom1.3, M_3_PinHeaderLeft1.3, M_3_PinHeaderRight1.3, M_3_PinHeaderTop1.3, M_3_U1.7 (VSS), M_3_U6.2 (GND)
Board_3-Net-(LED1-DOUT): M_3_LED1.4 (DOUT), M_3_LED2.2 (DIN)
Board_3-Net-(LED2-DOUT): M_3_LED2.4 (DOUT), M_3_LED3.2 (DIN)
Board_3-Net-(LED3-DOUT): M_3_LED3.4 (DOUT), M_3_LED4.2 (DIN)
Board_4-+5V: M_4_C1.2, M_4_C2.2, M_4_C4.1, M_4_J1.2, M_4_LED1.3 (VDD), M_4_LED2.3 (VDD), M_4_LED3.3 (VDD), M_4_LED4.3 (VDD), M_4_PinHeaderBottom1.1, M_4_PinHeaderLeft1.1, M_4_PinHeaderRight1.1, M_4_PinHeaderTop1.1, M_4_R1.1, M_4_R2.1, M_4_R3.1, M_4_R4.1, M_4_R5.1, M_4_R6.1, M_4_R7.1, M_4_R8.1, M_4_U1.9 (VCC), M_4_U6.1 (VDD)
Board_4-/DataBottom1: M_4_PinHeaderBottom1.2, M_4_R6.2, M_4_U1.17 (PA1)
Board_4-/DataBottom2: M_4_PinHeaderBottom1.4, M_4_R5.2, M_4_U1.16 (PA0)
Board_4-/DataLeft1: M_4_PinHeaderLeft1.2, M_4_R8.2, M_4_U1.12 (PB3)
Board_4-/DataLeft2: M_4_PinHeaderLeft1.4, M_4_R7.2, M_4_U1.11 (PB4)
Board_4-/DataRight1: M_4_PinHeaderRight1.2, M_4_R4.2, M_4_U1.1 (PA5)
Board_4-/DataRight2: M_4_PinHeaderRight1.4, M_4_R3.2, M_4_U1.2 (PA6)
Board_4-/DataTop1: M_4_PinHeaderTop1.2, M_4_R2.2, M_4_U1.6 (PB7)
Board_4-/DataTop2: M_4_PinHeaderTop1.4, M_4_R1.2, M_4_U1.5 (PC1)
Board_4-/HallAdc: M_4_C3.2, M_4_U1.20 (PA4), M_4_U6.3 (OUT)
Board_4-/LedIn: M_4_LED1.2 (DIN), M_4_U1.13 (PB2)
Board_4-/Reset: M_4_J1.5, M_4_U1.4 (PC0-NRST)
Board_4-/SWC: M_4_J1.4, M_4_U1.18 (PA2-SWC)
Board_4-/SWD: M_4_J1.3, M_4_U1.8 (PB6-SWD)
Board_4-/ShieldBottomLeft: M_4_J3.1, M_4_U1.14 (PB1)
Board_4-/ShieldBottomRight: M_4_J5.1, M_4_U1.19 (PA3)
Board_4-/ShieldTopLeft: M_4_J2.1, M_4_U1.10 (PB5)
Board_4-/ShieldTopRight: M_4_J4.1, M_4_U1.3 (PA7)
Board_4-GND: M_4_C1.1, M_4_C2.1, M_4_C3.1, M_4_C4.2, M_4_J1.1, M_4_LED1.1 (GND), M_4_LED2.1 (GND), M_4_LED3.1 (GND), M_4_LED4.1 (GND), M_4_PinHeaderBottom1.3, M_4_PinHeaderLeft1.3, M_4_PinHeaderRight1.3, M_4_PinHeaderTop1.3, M_4_U1.7 (VSS), M_4_U6.2 (GND)
Board_4-Net-(LED1-DOUT): M_4_LED1.4 (DOUT), M_4_LED2.2 (DIN)
Board_4-Net-(LED2-DOUT): M_4_LED2.4 (DOUT), M_4_LED3.2 (DIN)
Board_4-Net-(LED3-DOUT): M_4_LED3.4 (DOUT), M_4_LED4.2 (DIN)
Board_5-+5V: M_5_C1.2, M_5_C2.2, M_5_C4.1, M_5_J1.2, M_5_LED1.3 (VDD), M_5_LED2.3 (VDD), M_5_LED3.3 (VDD), M_5_LED4.3 (VDD), M_5_PinHeaderBottom1.1, M_5_PinHeaderLeft1.1, M_5_PinHeaderRight1.1, M_5_PinHeaderTop1.1, M_5_R1.1, M_5_R2.1, M_5_R3.1, M_5_R4.1, M_5_R5.1, M_5_R6.1, M_5_R7.1, M_5_R8.1, M_5_U1.9 (VCC), M_5_U6.1 (VDD)
Board_5-/DataBottom1: M_5_PinHeaderBottom1.2, M_5_R6.2, M_5_U1.17 (PA1)
Board_5-/DataBottom2: M_5_PinHeaderBottom1.4, M_5_R5.2, M_5_U1.16 (PA0)
Board_5-/DataLeft1: M_5_PinHeaderLeft1.2, M_5_R8.2, M_5_U1.12 (PB3)
Board_5-/DataLeft2: M_5_PinHeaderLeft1.4, M_5_R7.2, M_5_U1.11 (PB4)
Board_5-/DataRight1: M_5_PinHeaderRight1.2, M_5_R4.2, M_5_U1.1 (PA5)
Board_5-/DataRight2: M_5_PinHeaderRight1.4, M_5_R3.2, M_5_U1.2 (PA6)
Board_5-/DataTop1: M_5_PinHeaderTop1.2, M_5_R2.2, M_5_U1.6 (PB7)
Board_5-/DataTop2: M_5_PinHeaderTop1.4, M_5_R1.2, M_5_U1.5 (PC1)
Board_5-/HallAdc: M_5_C3.2, M_5_U1.20 (PA4), M_5_U6.3 (OUT)
Board_5-/LedIn: M_5_LED1.2 (DIN), M_5_U1.13 (PB2)
Board_5-/Reset: M_5_J1.5, M_5_U1.4 (PC0-NRST)
Board_5-/SWC: M_5_J1.4, M_5_U1.18 (PA2-SWC)
Board_5-/SWD: M_5_J1.3, M_5_U1.8 (PB6-SWD)
Board_5-/ShieldBottomLeft: M_5_J3.1, M_5_U1.14 (PB1)
Board_5-/ShieldBottomRight: M_5_J5.1, M_5_U1.19 (PA3)
Board_5-/ShieldTopLeft: M_5_J2.1, M_5_U1.10 (PB5)
Board_5-/ShieldTopRight: M_5_J4.1, M_5_U1.3 (PA7)
Board_5-GND: M_5_C1.1, M_5_C2.1, M_5_C3.1, M_5_C4.2, M_5_J1.1, M_5_LED1.1 (GND), M_5_LED2.1 (GND), M_5_LED3.1 (GND), M_5_LED4.1 (GND), M_5_PinHeaderBottom1.3, M_5_PinHeaderLeft1.3, M_5_PinHeaderRight1.3, M_5_PinHeaderTop1.3, M_5_U1.7 (VSS), M_5_U6.2 (GND)
Board_5-Net-(LED1-DOUT): M_5_LED1.4 (DOUT), M_5_LED2.2 (DIN)
Board_5-Net-(LED2-DOUT): M_5_LED2.4 (DOUT), M_5_LED3.2 (DIN)
Board_5-Net-(LED3-DOUT): M_5_LED3.4 (DOUT), M_5_LED4.2 (DIN)
Board_6-+5V: POGO_6_J2.1, POGO_6_J4.1, POGO_6_J5.1, POGO_6_J5.2, POGO_6_J5.3, POGO_6_J5.4, POGO_6_U1.1
Board_6-/Data1: POGO_6_J2.2, POGO_6_U2.1
Board_6-/Data2: POGO_6_J2.4, POGO_6_J3.1
Board_6-GND: POGO_6_J1.1, POGO_6_J2.3, POGO_6_U3.1
Board_7-+5V: POGO_7_J2.1, POGO_7_J4.1, POGO_7_J5.1, POGO_7_J5.2, POGO_7_J5.3, POGO_7_J5.4, POGO_7_U1.1
Board_7-/Data1: POGO_7_J2.2, POGO_7_U2.1
Board_7-/Data2: POGO_7_J2.4, POGO_7_J3.1
Board_7-GND: POGO_7_J1.1, POGO_7_J2.3, POGO_7_U3.1
Board_8-+5V: POGO_8_J2.1, POGO_8_J4.1, POGO_8_J5.1, POGO_8_J5.2, POGO_8_J5.3, POGO_8_J5.4, POGO_8_U1.1
Board_8-/Data1: POGO_8_J2.2, POGO_8_U2.1
Board_8-/Data2: POGO_8_J2.4, POGO_8_J3.1
Board_8-GND: POGO_8_J1.1, POGO_8_J2.3, POGO_8_U3.1
Board_9-+5V: POGO_9_J2.1, POGO_9_J4.1, POGO_9_J5.1, POGO_9_J5.2, POGO_9_J5.3, POGO_9_J5.4, POGO_9_U1.1
Board_9-/Data1: POGO_9_J2.2, POGO_9_U2.1
Board_9-/Data2: POGO_9_J2.4, POGO_9_J3.1
Board_9-GND: POGO_9_J1.1, POGO_9_J2.3, POGO_9_U3.1
Board_10-+5V: POGO_10_J2.1, POGO_10_J4.1, POGO_10_J5.1, POGO_10_J5.2, POGO_10_J5.3, POGO_10_J5.4, POGO_10_U1.1
Board_10-/Data1: POGO_10_J2.2, POGO_10_U2.1
Board_10-/Data2: POGO_10_J2.4, POGO_10_J3.1
Board_10-GND: POGO_10_J1.1, POGO_10_J2.3, POGO_10_U3.1
Board_11-+5V: POGO_11_J2.1, POGO_11_J4.1, POGO_11_J5.1, POGO_11_J5.2, POGO_11_J5.3, POGO_11_J5.4, POGO_11_U1.1
Board_11-/Data1: POGO_11_J2.2, POGO_11_U2.1
Board_11-/Data2: POGO_11_J2.4, POGO_11_J3.1
Board_11-GND: POGO_11_J1.1, POGO_11_J2.3, POGO_11_U3.1
Board_12-+5V: POGO_12_J2.1, POGO_12_J4.1, POGO_12_J5.1, POGO_12_J5.2, POGO_12_J5.3, POGO_12_J5.4, POGO_12_U1.1
Board_12-/Data1: POGO_12_J2.2, POGO_12_U2.1
Board_12-/Data2: POGO_12_J2.4, POGO_12_J3.1
Board_12-GND: POGO_12_J1.1, POGO_12_J2.3, POGO_12_U3.1
Board_13-+5V: POGO_13_J2.1, POGO_13_J4.1, POGO_13_J5.1, POGO_13_J5.2, POGO_13_J5.3, POGO_13_J5.4, POGO_13_U1.1
Board_13-/Data1: POGO_13_J2.2, POGO_13_U2.1
Board_13-/Data2: POGO_13_J2.4, POGO_13_J3.1
Board_13-GND: POGO_13_J1.1, POGO_13_J2.3, POGO_13_U3.1
Board_14-+5V: POGO_14_J2.1, POGO_14_J4.1, POGO_14_J5.1, POGO_14_J5.2, POGO_14_J5.3, POGO_14_J5.4, POGO_14_U1.1
Board_14-/Data1: POGO_14_J2.2, POGO_14_U2.1
Board_14-/Data2: POGO_14_J2.4, POGO_14_J3.1
Board_14-GND: POGO_14_J1.1, POGO_14_J2.3, POGO_14_U3.1
Board_15-+5V: POGO_15_J2.1, POGO_15_J4.1, POGO_15_J5.1, POGO_15_J5.2, POGO_15_J5.3, POGO_15_J5.4, POGO_15_U1.1
Board_15-/Data1: POGO_15_J2.2, POGO_15_U2.1
Board_15-/Data2: POGO_15_J2.4, POGO_15_J3.1
Board_15-GND: POGO_15_J1.1, POGO_15_J2.3, POGO_15_U3.1
Board_16-+5V: POGO_16_J2.1, POGO_16_J4.1, POGO_16_J5.1, POGO_16_J5.2, POGO_16_J5.3, POGO_16_J5.4, POGO_16_U1.1
Board_16-/Data1: POGO_16_J2.2, POGO_16_U2.1
Board_16-/Data2: POGO_16_J2.4, POGO_16_J3.1
Board_16-GND: POGO_16_J1.1, POGO_16_J2.3, POGO_16_U3.1
Board_17-+5V: POGO_17_J2.1, POGO_17_J4.1, POGO_17_J5.1, POGO_17_J5.2, POGO_17_J5.3, POGO_17_J5.4, POGO_17_U1.1
Board_17-/Data1: POGO_17_J2.2, POGO_17_U2.1
Board_17-/Data2: POGO_17_J2.4, POGO_17_J3.1
Board_17-GND: POGO_17_J1.1, POGO_17_J2.3, POGO_17_U3.1
Board_18-+5V: POGO_18_J2.1, POGO_18_J4.1, POGO_18_J5.1, POGO_18_J5.2, POGO_18_J5.3, POGO_18_J5.4, POGO_18_U1.1
Board_18-/Data1: POGO_18_J2.2, POGO_18_U2.1
Board_18-/Data2: POGO_18_J2.4, POGO_18_J3.1
Board_18-GND: POGO_18_J1.1, POGO_18_J2.3, POGO_18_U3.1
Board_19-+5V: POGO_19_J2.1, POGO_19_J4.1, POGO_19_J5.1, POGO_19_J5.2, POGO_19_J5.3, POGO_19_J5.4, POGO_19_U1.1
Board_19-/Data1: POGO_19_J2.2, POGO_19_U2.1
Board_19-/Data2: POGO_19_J2.4, POGO_19_J3.1
Board_19-GND: POGO_19_J1.1, POGO_19_J2.3, POGO_19_U3.1
Board_20-+5V: POGO_20_J2.1, POGO_20_J4.1, POGO_20_J5.1, POGO_20_J5.2, POGO_20_J5.3, POGO_20_J5.4, POGO_20_U1.1
Board_20-/Data1: POGO_20_J2.2, POGO_20_U2.1
Board_20-/Data2: POGO_20_J2.4, POGO_20_J3.1
Board_20-GND: POGO_20_J1.1, POGO_20_J2.3, POGO_20_U3.1
Board_21-+5V: POGO_21_J2.1, POGO_21_J4.1, POGO_21_J5.1, POGO_21_J5.2, POGO_21_J5.3, POGO_21_J5.4, POGO_21_U1.1
Board_21-/Data1: POGO_21_J2.2, POGO_21_U2.1
Board_21-/Data2: POGO_21_J2.4, POGO_21_J3.1
Board_21-GND: POGO_21_J1.1, POGO_21_J2.3, POGO_21_U3.1
Board_22-+5V: POGO_22_J2.1, POGO_22_J4.1, POGO_22_J5.1, POGO_22_J5.2, POGO_22_J5.3, POGO_22_J5.4, POGO_22_U1.1
Board_22-/Data1: POGO_22_J2.2, POGO_22_U2.1
Board_22-/Data2: POGO_22_J2.4, POGO_22_J3.1
Board_22-GND: POGO_22_J1.1, POGO_22_J2.3, POGO_22_U3.1
Board_23-+5V: POGO_23_J2.1, POGO_23_J4.1, POGO_23_J5.1, POGO_23_J5.2, POGO_23_J5.3, POGO_23_J5.4, POGO_23_U1.1
Board_23-/Data1: POGO_23_J2.2, POGO_23_U2.1
Board_23-/Data2: POGO_23_J2.4, POGO_23_J3.1
Board_23-GND: POGO_23_J1.1, POGO_23_J2.3, POGO_23_U3.1
Board_24-+5V: POGO_24_J2.1, POGO_24_J4.1, POGO_24_J5.1, POGO_24_J5.2, POGO_24_J5.3, POGO_24_J5.4, POGO_24_U1.1
Board_24-/Data1: POGO_24_J2.2, POGO_24_U2.1
Board_24-/Data2: POGO_24_J2.4, POGO_24_J3.1
Board_24-GND: POGO_24_J1.1, POGO_24_J2.3, POGO_24_U3.1
Board_25-+5V: POGO_25_J2.1, POGO_25_J4.1, POGO_25_J5.1, POGO_25_J5.2, POGO_25_J5.3, POGO_25_J5.4, POGO_25_U1.1
Board_25-/Data1: POGO_25_J2.2, POGO_25_U2.1
Board_25-/Data2: POGO_25_J2.4, POGO_25_J3.1
Board_25-GND: POGO_25_J1.1, POGO_25_J2.3, POGO_25_U3.1
Board_26-+5V: POGO_26_J2.1, POGO_26_J4.1, POGO_26_J5.1, POGO_26_J5.2, POGO_26_J5.3, POGO_26_J5.4, POGO_26_U1.1
Board_26-/Data1: POGO_26_J2.2, POGO_26_U2.1
Board_26-/Data2: POGO_26_J2.4, POGO_26_J3.1
Board_26-GND: POGO_26_J1.1, POGO_26_J2.3, POGO_26_U3.1
Board_27-+5V: POGO_27_J2.1, POGO_27_J4.1, POGO_27_J5.1, POGO_27_J5.2, POGO_27_J5.3, POGO_27_J5.4, POGO_27_U1.1
Board_27-/Data1: POGO_27_J2.2, POGO_27_U2.1
Board_27-/Data2: POGO_27_J2.4, POGO_27_J3.1
Board_27-GND: POGO_27_J1.1, POGO_27_J2.3, POGO_27_U3.1
Board_28-+5V: POGO_28_J2.1, POGO_28_J4.1, POGO_28_J5.1, POGO_28_J5.2, POGO_28_J5.3, POGO_28_J5.4, POGO_28_U1.1
Board_28-/Data1: POGO_28_J2.2, POGO_28_U2.1
Board_28-/Data2: POGO_28_J2.4, POGO_28_J3.1
Board_28-GND: POGO_28_J1.1, POGO_28_J2.3, POGO_28_U3.1
Board_29-+5V: POGO_29_J2.1, POGO_29_J4.1, POGO_29_J5.1, POGO_29_J5.2, POGO_29_J5.3, POGO_29_J5.4, POGO_29_U1.1
Board_29-/Data1: POGO_29_J2.2, POGO_29_U2.1
Board_29-/Data2: POGO_29_J2.4, POGO_29_J3.1
Board_29-GND: POGO_29_J1.1, POGO_29_J2.3, POGO_29_U3.1

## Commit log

2025-11-22 Initial design
2025-11-22 Prevent accidental short circuit and add basic box 3d model freecad
2025-11-22 Fix .gitignore locations
2025-11-23 Update PCB
2025-11-23 Add hall sensor shield
2025-11-23 Add cadquery for automatic 3d model generation
2025-11-23 Update smart cube 3d model
2025-11-23 Add magnet holders
2025-11-23 Add smart cube panel
2025-11-24 Fix 3d model paths
2025-11-24 Fix 3d model output path
2025-11-24 Fix magnet holder, add todo
2025-11-24 Fix magnet holder wall thickness
2025-11-24 Add power supply (wip) and update panel
2025-11-27 Finish module, power supply and connector design, panel is wip
2025-11-28 Fix partitionlines generation
2025-11-28 Finish panel script
2025-11-28 Update 3d case
2025-11-28 Add Power Supply case
2025-11-28 Update box to have a diagonal split angle
2025-11-28 Fix diagonal split angle
2025-11-28 Fix diagonal split angle (again)
2025-11-28 Fix power supply module offset shape
2025-11-28 Add clip connector
2025-11-28 Fix mistake in pogo pin compression calculation
2025-11-28 Fix broken clip connector
2025-11-28 Add Firmware (hopefully it works)
2025-11-29 Move Firmware to new folder
2025-11-29 Add some documentation
2025-11-30 Fix led pin 1 indicator not visible causing jlcpcb polarity confirmation request email
2025-11-30 Fix some enclosure tolerances for a better fit
2025-12-08 Maybe fix box wiggle problems
2025-12-08 Fix flash task
2025-12-08 Add reset after flashing
2025-12-08 Implement basic led toggling
2025-12-08 Create a nice color effect for testing
2025-12-08 Remove unused code
2025-12-09 Create led api
2025-12-09 fix delays
2025-12-09 60% compression is enough
2025-12-09 Add todo
2025-12-10 Redesign cube enclosure
2025-12-10 Add chamfers for a nicer look
2025-12-11 fix some tolerances
2025-12-11 closer magnets lead to bumps in the case so the cases are not flat anymore
2025-12-12 Enable brownout detection
2025-12-13 Smaller magnet tolerances
2025-12-13 Add debug launch config
2025-12-13 Add magnet snap fit and smaller box top thickness
2025-12-13 Add button cutouts to power supply enclosure
2025-12-13 Reduce magnet wall thickness
2025-12-13 Implement data reading
2025-12-13 fix tolerances
2025-12-13 Add electrolytic bulk capacitors to modules and power supply
2025-12-14 Implement simple cube data transfer
2025-12-14 Refactor simple data transfer to use callbacks
2025-12-14 Reduce code nesting
2025-12-14 Add some docs
2025-12-14 Replace words with bytes for sending data
2025-12-14 Fix cube not going into idle mode on error
2025-12-14 Fix connecting cubes at the same time not working
2025-12-14 Add hall sensor initialization
2025-12-17 Update pcbs
2025-12-17 Improve clip connector
2025-12-17 Implement data simpler transfer api
2025-12-17 Improve cube data, add cube position data placeholder
2025-12-18 Implement full grid position calculation
2025-12-18 Improve position algorithm
2025-12-18 Refactor cube
2025-12-18 Implement new failsafe connection protocol (which later prevents circles in connection graph)
2025-12-18 Remove debug delays
2025-12-18 Reorganize folders and files
2025-12-19 Add timing protocol diagrams
2025-12-19 Fix timing protocol diagram
2025-12-19 Implement parent detection protocol
